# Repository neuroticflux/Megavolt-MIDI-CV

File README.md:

# Megavolt-MIDI-CV
ATmega328-based modular synth MIDI-CV interface

The Megavolt is a MIDI-CV interface featuring two high quality 12-bit CV outputs for note and pitchbend, four 8-bit CV outputs for MIDI CC's, as well as GATE output, two CLOCK outputs and note glide.

12-bit CVs:
CV 1: MIDI note (with glide amount pot)
CV 2: Pitchbend

MIDI NOTE ON triggers the GATE output HIGH. MIDI NOTE OFF triggers it low.

8-bit CVs:
CV 3: CC #01 (Modwheel)
CV 4: CC #04 (Aftertouch/foot controller)
CV 5: CC #16 (General purpose)
CV 6: Velocity

The two CLOCK jacks output 1/1' and 1/16' ticks the from incoming MIDI clock.

A note stack of 4 notes allows several keys to be held down in succession and released to return to the previous note in the stack, allowing for fast playing of arpeggios etc.

The interface is made to hook up to a PSU delivering +/-15V as well as +5V (Synthesizers.com standard).
Current draw untested.

TODO:

- Eurorack compatibility
- Detect MIDI channel on first incoming message
- Reverse voltage protection diodes on input

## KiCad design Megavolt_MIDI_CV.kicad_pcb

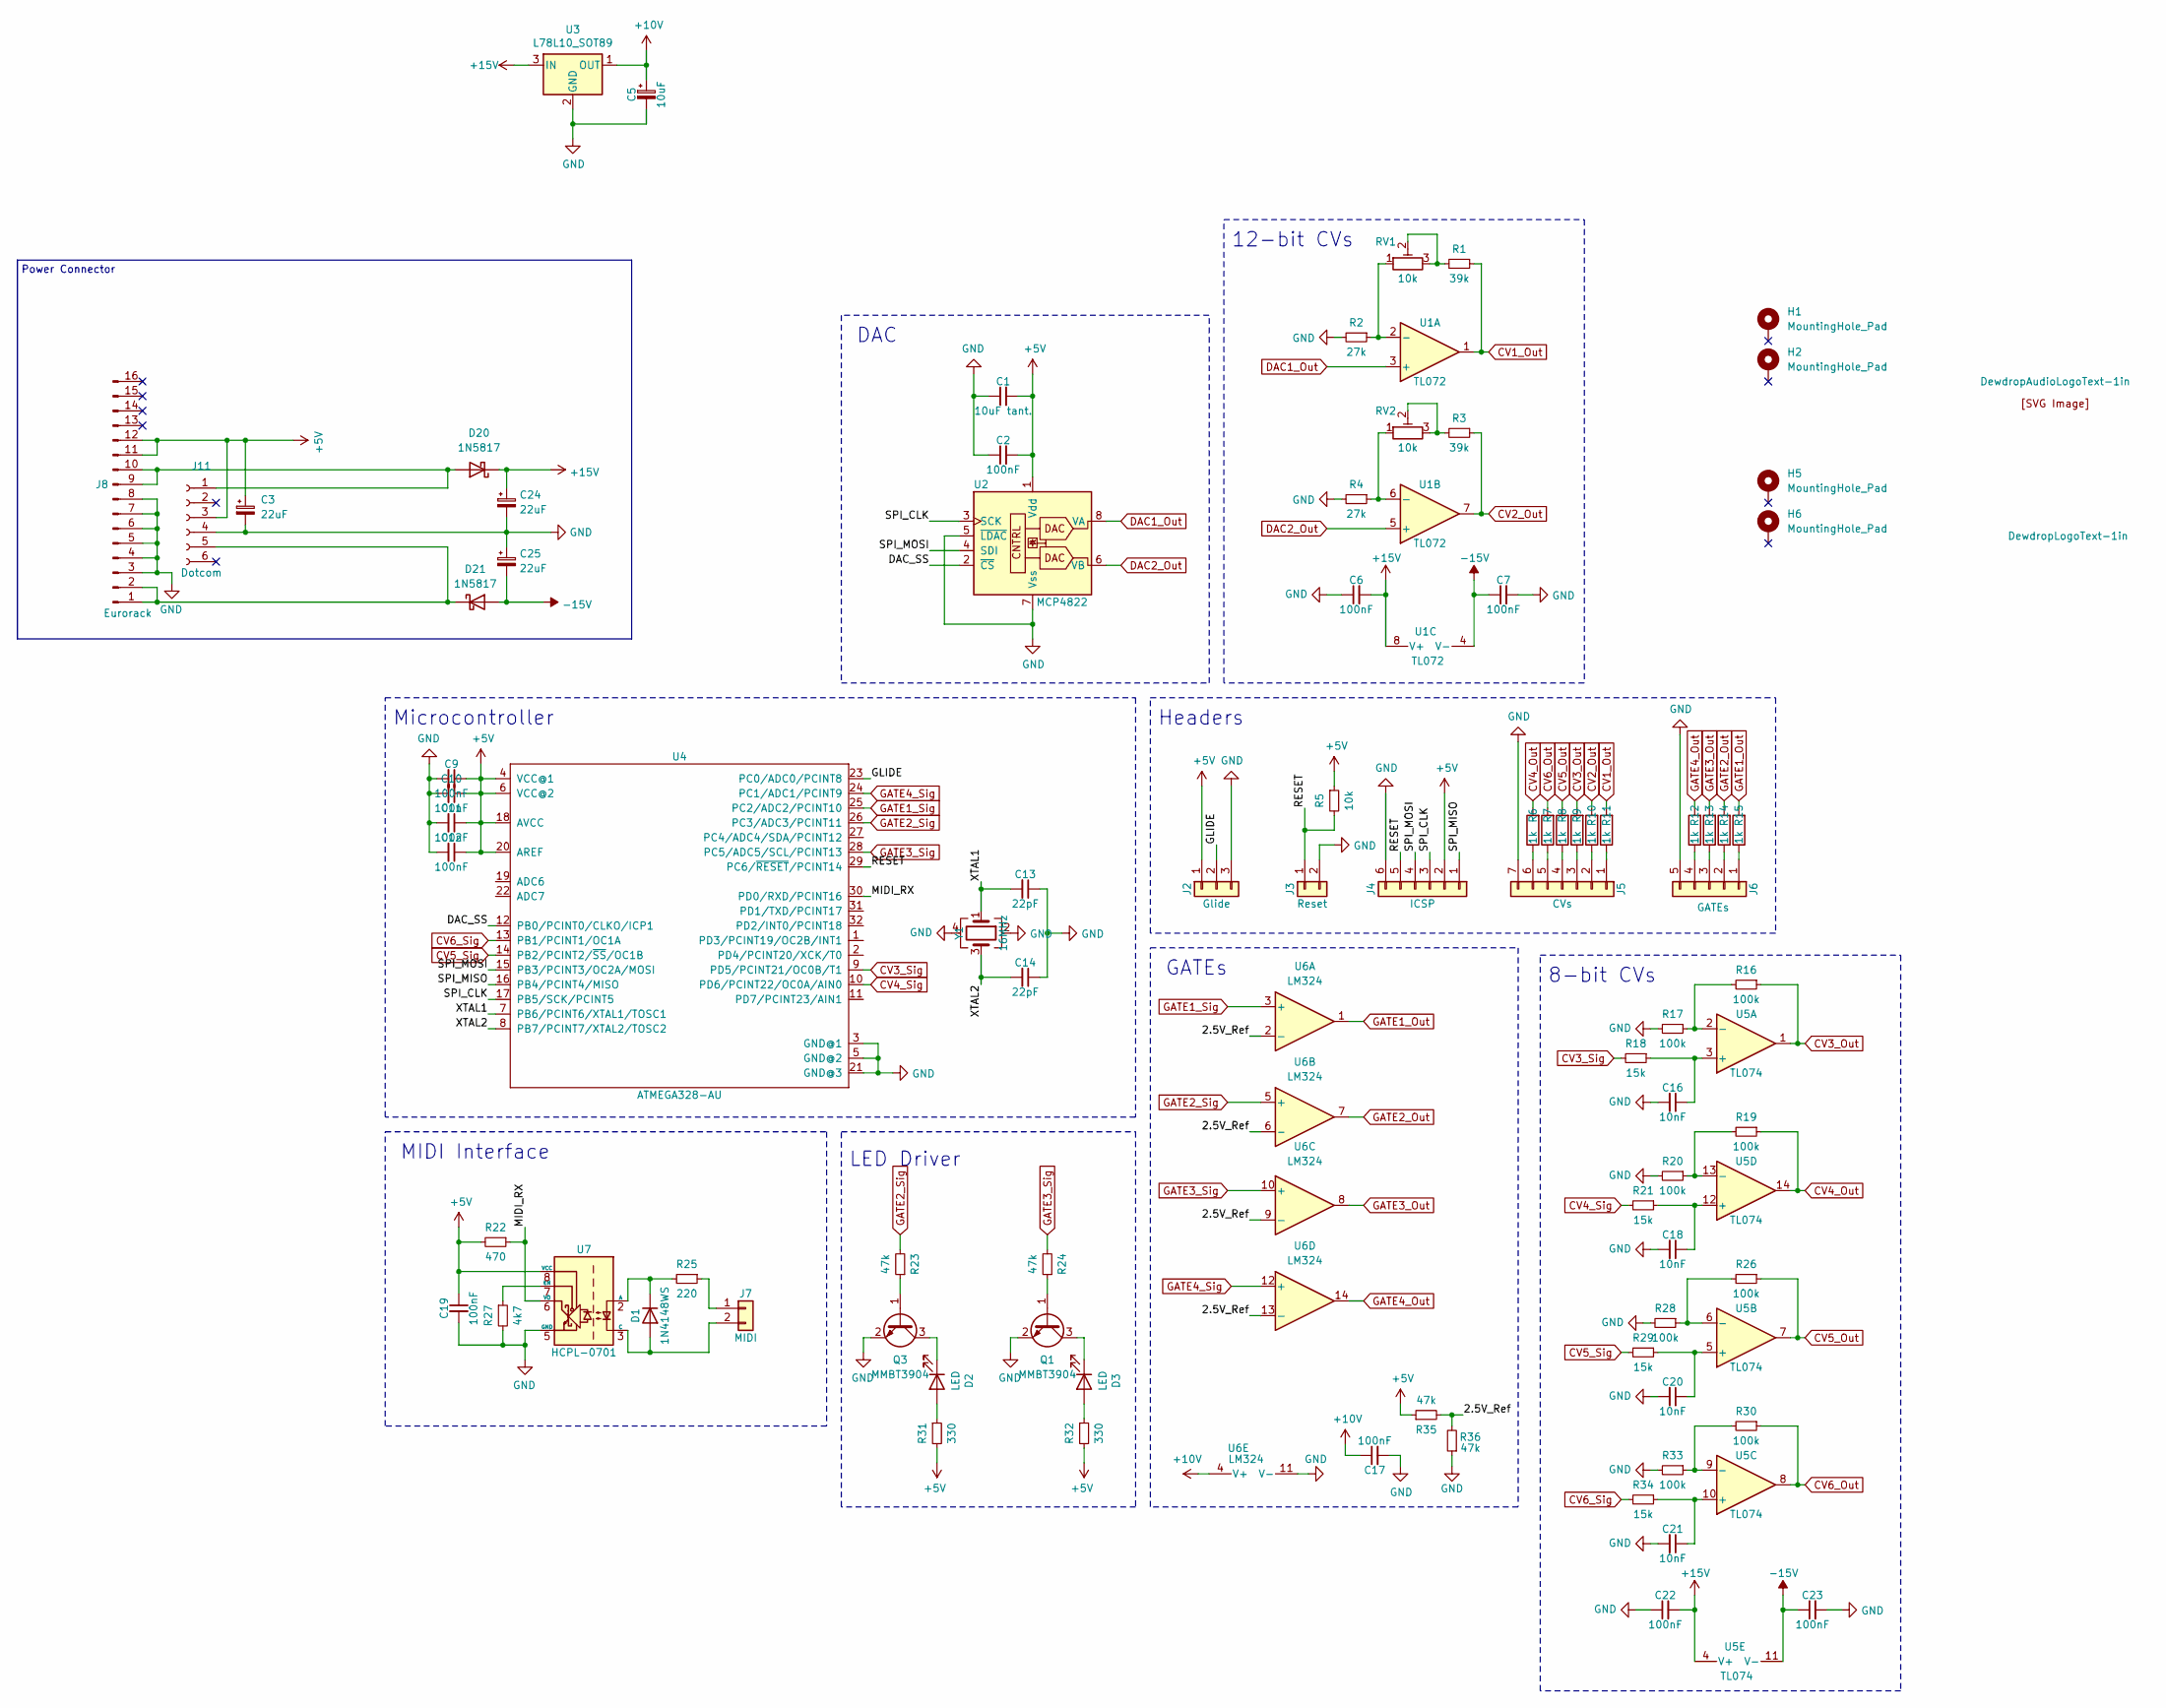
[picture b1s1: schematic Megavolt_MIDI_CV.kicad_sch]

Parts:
C1: 10uF tant.; CP_EIA-3216-18_Kemet-A
C2, C6, C7, C9, C10, C11, C12, C17, C19, C22, C23: 100nF; C_0603_1608Metric
C3, C24, C25: 22uF; CP_Radial_D6.3mm_P2.50mm
C5: 10uF; CP_Radial_D5.0mm_P2.50mm
C13, C14: 22pF; C_0402_1005Metric
C16, C18, C20, C21: 10nF; C_0603_1608Metric
D1: 1N4148WS; D_SOD-323
D2, D3: LED; PinHeader_1x02_P2.54mm_Vertical
D20, D21: 1N5817; D_SOD-123
H1, H2, H5, H6: MountingHole_Pad; MountingHole_3.2mm_M3_DIN965_Pad
J2: Glide; PinHeader_1x03_P2.54mm_Vertical
J3: Reset; PinHeader_1x02_P2.54mm_Vertical
J4: ICSP; PinHeader_2x03_P2.54mm_Vertical
J5: CVs; PinHeader_1x07_P2.54mm_Vertical
J6: GATEs; PinHeader_1x05_P2.54mm_Vertical
J7: MIDI; PinHeader_1x02_P2.54mm_Vertical
J8: Eurorack; PinHeader_2x08_P2.54mm_Vertical
J11: Dotcom; Molex_KK-254_AE-6410-06A_1x06_P2.54mm_Vertical
LOGO2: DewdropLogoText-1in
LOGO3: DewdropAudioLogoText-1in; DewdropAudioLogo-1in
Q1, Q3: MMBT3904; SOT-23
R1, R3: 39k; R_0402_1005Metric
R2, R4: 27k; R_0402_1005Metric
R5: 10k; R_0402_1005Metric
R6, R7, R8, R9, R10, R11, R12, R13, R14, R15: 1k; R_0603_1608Metric
R16, R17, R19, R20, R26, R28, R30, R33: 100k; R_0402_1005Metric
R18, R21, R29, R34: 15k; R_0402_1005Metric
R22: 470; R_0603_1608Metric
R23, R24: 47k; R_0603_1608Metric
R25: 220; R_0402_1005Metric
R27: 4k7; R_0402_1005Metric
R31, R32: 330; R_0805_2012Metric
R35, R36: 47k; R_0402_1005Metric
RV1, RV2: 10k; Potentiometer_Bourns_3314J_Vertical
U1: TL072; SOIC-8_3.9x4.9mm_P1.27mm
U2: MCP4822; SOIC-8_3.9x4.9mm_P1.27mm
U3: L78L10_SOT89; SOT-89-3
U4: ATMEGA328-AU; LQFP-32_7x7mm_P0.8mm
U5: TL074; SOIC-14_3.9x8.7mm_P1.27mm
U6: LM324; SOIC-14_3.9x8.7mm_P1.27mm
U7: HCPL-0701; SOIC-8_3.9x4.9mm_P1.27mm
Y1: 16MHz; Crystal_SMD_3225-4Pin_3.2x2.5mm

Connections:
+5V: C1.2, C2.2, C3.1, C9.1, C10.1, C11.1, C12.1, C19.1, J2.1, J4.2, J8.11, J8.12, J11.3, R5.1, R22.2, R31.2, R32.2, R35.1, U2.1 (Vdd), U4.4 (VCC@1), U4.6 (VCC@2), U4.18 (AVCC), U4.20 (AREF), U7.8 (VCC)
+10V: C5.1, C17.1, U3.1 (OUT), U6.4 (V+)
+15V: C6.2, C22.2, C24.1, D20.1 (K), U1.8 (V+), U3.3 (IN), U5.4 (V+)
-15V: C7.1, C23.1, C25.2, D21.2 (A), U1.4 (V-), U5.11 (V-)
/2.5V_Ref: R35.2, R36.2, U6.2 (-), U6.6 (-), U6.9 (-), U6.13 (-)
/DAC_SS: U2.2 (~CS), U4.12 (PB0/PCINT0/CLKO/ICP1)
/GLIDE: J2.2, U4.23 (PC0/ADC0/PCINT8)
/MIDI_RX: R22.1, U4.30 (PD0/RXD/PCINT16), U7.6 (VO)
/RESET: J3.1, J4.5, R5.2, U4.29 (PC6/~RESET/PCINT14)
/SPI_CLK: J4.3, U2.3 (SCK), U4.17 (PB5/SCK/PCINT5)
/SPI_MISO: J4.1, U4.16 (PB4/PCINT4/MISO)
/SPI_MOSI: J4.4, U2.4 (SDI), U4.15 (PB3/PCINT3/OC2A/MOSI)
/XTAL1: C13.2, U4.7 (PB6/PCINT6/XTAL1/TOSC1), Y1.1
/XTAL2: C14.2, U4.8 (PB7/PCINT7/XTAL2/TOSC2), Y1.3
CV1_Out: R1.1, R11.2, U1.1
CV2_Out: R3.1, R10.2, U1.7
CV3_Out: R9.2, R16.1, U5.1
CV3_Sig: R18.2, U4.9 (PD5/PCINT21/OC0B/T1)
CV4_Out: R6.2, R19.1, U5.14
CV4_Sig: R21.2, U4.10 (PD6/PCINT22/OC0A/AIN0)
CV5_Out: R8.2, R26.1, U5.7
CV5_Sig: R29.2, U4.14 (PB2/PCINT2/~SS/OC1B)
CV6_Out: R7.2, R30.1, U5.8
CV6_Sig: R34.2, U4.13 (PB1/PCINT1/OC1A)
DAC1_Out: U1.3 (+), U2.8 (VA)
DAC2_Out: U1.5 (+), U2.6 (VB)
GATE1_Out: R15.2, U6.1
GATE1_Sig: U4.25 (PC2/ADC2/PCINT10), U6.3 (+)
GATE2_Out: R14.2, U6.7
GATE2_Sig: R23.2, U4.26 (PC3/ADC3/PCINT11), U6.5 (+)
GATE3_Out: R13.2, U6.8
GATE3_Sig: R24.2, U4.28 (PC5/ADC5/SCL/PCINT13), U6.10 (+)
GATE4_Out: R12.2, U6.14
GATE4_Sig: U4.24 (PC1/ADC1/PCINT9), U6.12 (+)
GND: C1.1, C2.1, C3.2, C5.2, C6.1, C7.2, C9.2, C10.2, C11.2, C12.2, C13.1, C14.1, C16.2, C17.2, C18.2, C19.2, C20.2, C21.2, C22.1, C23.2, C24.2, C25.1, J2.3, J3.2, J4.6, J5.7, J6.5, J8.3, J8.4, J8.5, J8.6, J8.7, J8.8, J11.4, Q1.2 (E), Q3.2 (E), R2.2, R4.2, R17.2, R20.2, R27.2, R28.2, R33.2, R36.1, U2.5 (~LDAC), U2.7 (Vss), U3.2 (GND), U4.3 (GND@1), U4.5 (GND@2), U4.21 (GND@3), U6.11 (V-), U7.5 (GND), Y1.2, Y1.4
unnamed: D1.2 (A), J7.2, U7.3 (C)
unnamed: D1.1 (K), R25.2, U7.2 (A)
unnamed: D2.2 (A), R31.1
unnamed: D2.1 (K), Q3.3 (C)
unnamed: D3.2 (A), R32.1
unnamed: D3.1 (K), Q1.3 (C)
unnamed: D20.2 (A), J8.9, J8.10, J11.1
unnamed: D21.1 (K), J8.1, J8.2, J11.5
unnamed: J5.1, R11.1
unnamed: J5.2, R10.1
unnamed: J5.3, R9.1
unnamed: J5.4, R8.1
unnamed: J5.5, R7.1
unnamed: J5.6, R6.1
unnamed: J6.1, R15.1
unnamed: J6.2, R14.1
unnamed: J6.3, R13.1
unnamed: J6.4, R12.1
unnamed: J7.1, R25.1
unnamed: Q1.1 (B), R24.1
unnamed: Q3.1 (B), R23.1
unnamed: R1.2, RV1.2, RV1.3
unnamed: R3.2, RV2.2, RV2.3
unnamed: R2.1, RV1.1, U1.2 (-)
unnamed: R4.1, RV2.1, U1.6 (-)
unnamed: C16.1, R18.1, U5.3 (+)
unnamed: R16.2, R17.1, U5.2 (-)
unnamed: C20.1, R29.1, U5.5 (+)
unnamed: R26.2, R28.1, U5.6 (-)
unnamed: C21.1, R34.1, U5.10 (+)
unnamed: R30.2, R33.1, U5.9 (-)
unnamed: C18.1, R21.1, U5.12 (+)
unnamed: R19.2, R20.1, U5.13 (-)
unnamed: R27.1, U7.7 (EN)

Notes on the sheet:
Headers
8-bit CVs
Microcontroller
GATEs
Power Connector
DAC
LED Driver
12-bit CVs
MIDI Interface

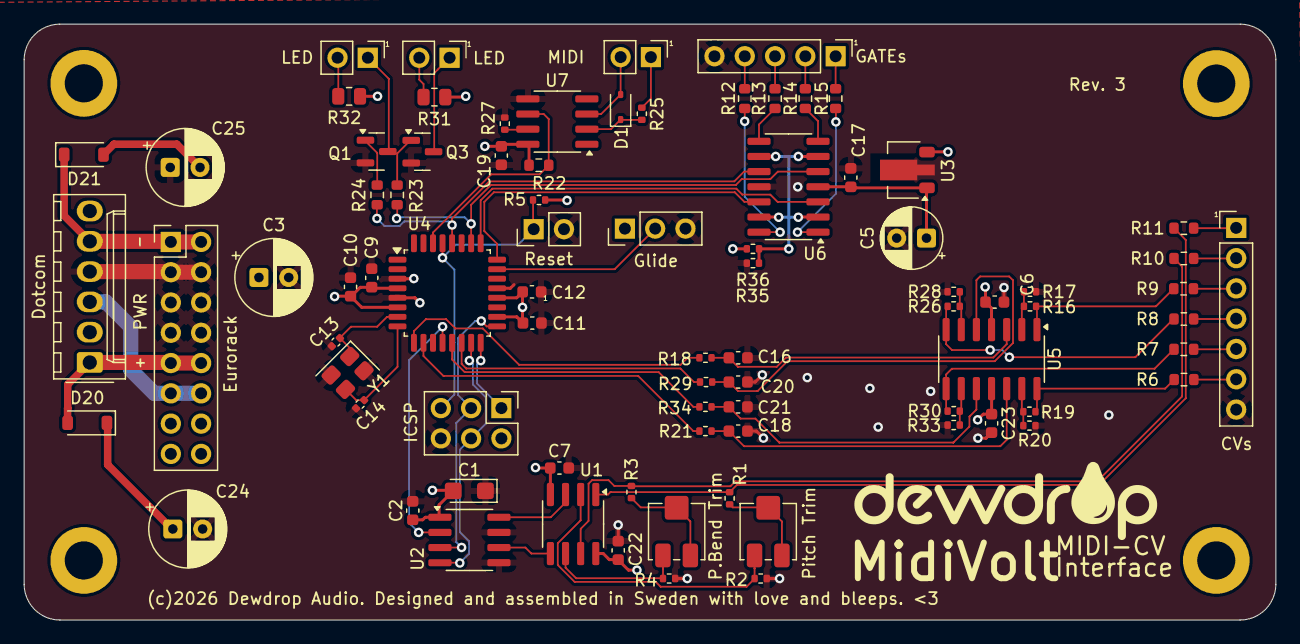
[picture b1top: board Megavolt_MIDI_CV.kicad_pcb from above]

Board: 4 copper layers, 105.0 x 50.0 mm, 89 parts (1 on the bottom side), 69 nets.

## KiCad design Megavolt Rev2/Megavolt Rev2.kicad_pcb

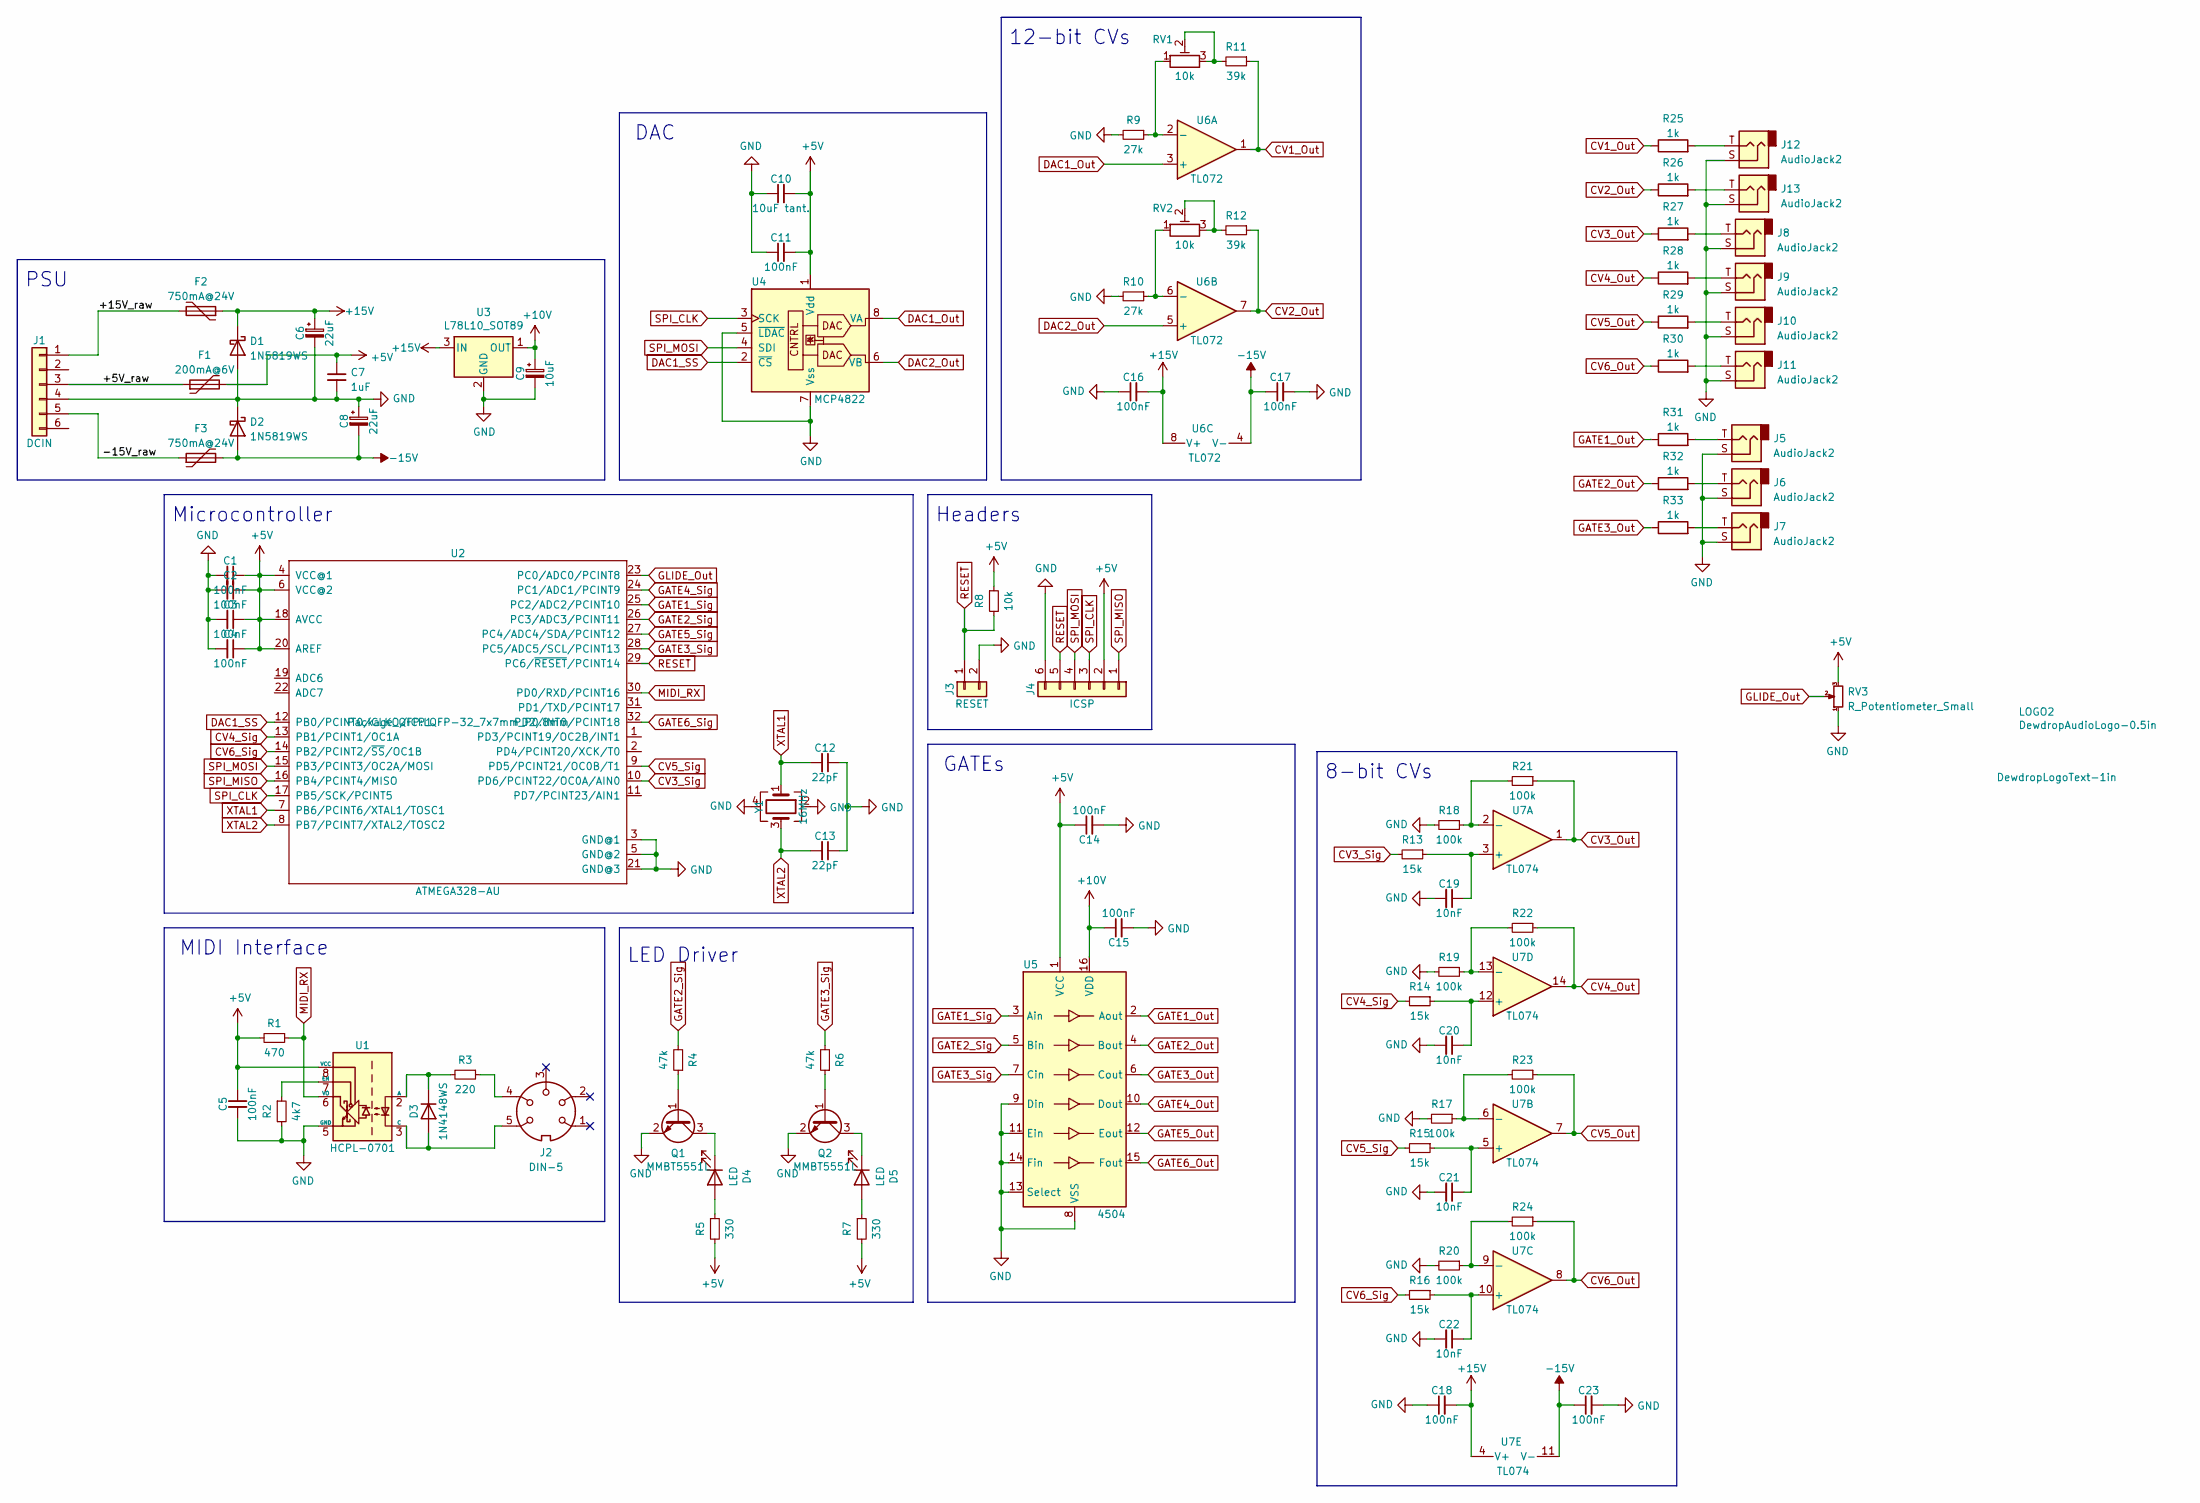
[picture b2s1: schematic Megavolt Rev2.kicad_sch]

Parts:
C1, C2, C3, C4, C5, C11, C14, C15, C16, C17, C18, C23: 100nF; C_0603_1608Metric
C6, C8: 22uF; CP_Radial_D5.0mm_P2.50mm
C7: 1uF; C_0805_2012Metric
C9: 10uF; CP_Radial_D5.0mm_P2.50mm
C10: 10uF tant.; CP_EIA-3216-18_Kemet-A
C12, C13: 22pF; C_0402_1005Metric
C19, C20, C21, C22: 10nF; C_0603_1608Metric
D1, D2: 1N5819WS; D_SOD-323
D3: 1N4148WS; D_SOD-323
D4, D5: LED; LED_D5.0mm
F1: 200mA@6V; Fuse_0402_1005Metric
F2, F3: 750mA@24V; Fuse_1812_4532Metric
J1: DCIN; Molex_KK-254_AE-6410-06A_1x06_P2.54mm_Vertical
J2: DIN-5; Switchcraft 57NC5FX
J3: RESET; PinHeader_1x02_P2.54mm_Vertical
J4: ICSP; PinHeader_2x03_P2.54mm_Vertical
J5, J6, J7, J8, J9, J10, J11, J12, J13: AudioJack2; Amphenol AJCM-MN-2
LOGO1: DewdropLogoText-1in
LOGO2: DewdropAudioLogo-0.5in
Q1, Q2: MMBT5551L; SOT-23
R1: 470; R_0603_1608Metric
R2: 4k7; R_0603_1608Metric
R3: 220; R_0603_1608Metric
R4, R6: 47k; R_0603_1608Metric
R5, R7: 330; R_0603_1608Metric
R8: 10k; R_0603_1608Metric
R9, R10: 27k; R_0603_1608Metric
R11, R12: 39k; R_0603_1608Metric
R13, R14, R15, R16: 15k; R_0603_1608Metric
R17, R18, R19, R20, R21, R22, R23, R24: 100k; R_0603_1608Metric
R25, R26, R27, R28, R29, R30, R31, R32, R33: 1k; R_0603_1608Metric
RV1, RV2: 10k; Potentiometer_Bourns_3314G_Vertical
RV3: R_Potentiometer_Small; Potentiometer_Alps_RK09L_Single_Vertical
U1: HCPL-0701; SOIC-8_3.9x4.9mm_P1.27mm
U2: ATMEGA328-AU; LQFP-32_7x7mm_P0.8mm
U3: L78L10_SOT89; SOT-89-3
U4: MCP4822; SOIC-8_3.9x4.9mm_P1.27mm
U5: 4504; SOIC-16_3.9x9.9mm_P1.27mm
U6: TL072; SOIC-8_3.9x4.9mm_P1.27mm
U7: TL074; SOIC-14_3.9x8.7mm_P1.27mm
Y1: 16MHz; Crystal_SMD_3225-4Pin_3.2x2.5mm

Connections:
+5V: C1.1, C2.1, C3.1, C4.1, C5.1, C7.1, C10.2, C11.2, C14.1, F1.2, J4.2, R1.2, R5.2, R7.2, R8.1, RV3.3, U1.8 (VCC), U2.4 (VCC@1), U2.6 (VCC@2), U2.18 (AVCC), U2.20 (AREF), U4.1 (Vdd), U5.1 (VCC)
+10V: C9.1, C15.1, U3.1 (OUT), U5.16 (VDD)
+15V: C6.1, C16.2, C18.2, D1.1 (K), F2.1, U3.3 (IN), U6.8 (V+), U7.4 (V+)
-15V: C8.2, C17.1, C23.1, D2.2 (A), F3.2, U6.4 (V-), U7.11 (V-)
/+5V_raw: F1.1, J1.3
/+15V_raw: F2.2, J1.1
/-15V_raw: F3.1, J1.5
CV1_Out: R11.1, R25.1, U6.1
CV2_Out: R12.1, R26.1, U6.7
CV3_Out: R21.1, R27.1, U7.1
CV3_Sig: R13.2, U2.10 (PD6/PCINT22/OC0A/AIN0)
CV4_Out: R22.1, R28.1, U7.14
CV4_Sig: R14.2, U2.13 (PB1/PCINT1/OC1A)
CV5_Out: R23.1, R29.1, U7.7
CV5_Sig: R15.2, U2.9 (PD5/PCINT21/OC0B/T1)
CV6_Out: R24.1, R30.1, U7.8
CV6_Sig: R16.2, U2.14 (PB2/PCINT2/~SS/OC1B)
DAC1_Out: U4.8 (VA), U6.3 (+)
DAC1_SS: U2.12 (PB0/PCINT0/CLKO/ICP1), U4.2 (~CS)
DAC2_Out: U4.6 (VB), U6.5 (+)
GATE1_Out: R31.1, U5.2 (Aout)
GATE1_Sig: U2.25 (PC2/ADC2/PCINT10), U5.3 (Ain)
GATE2_Out: R32.1, U5.4 (Bout)
GATE2_Sig: R4.2, U2.26 (PC3/ADC3/PCINT11), U5.5 (Bin)
GATE3_Out: R33.1, U5.6 (Cout)
GATE3_Sig: R6.2, U2.28 (PC5/ADC5/SCL/PCINT13), U5.7 (Cin)
GATE4_Out: U5.10 (Dout)
GATE4_Sig: U2.24 (PC1/ADC1/PCINT9)
GATE5_Out: U5.12 (Eout)
GATE5_Sig: U2.27 (PC4/ADC4/SDA/PCINT12)
GATE6_Out: U5.15 (Fout)
GATE6_Sig: U2.32 (PD2/INT0/PCINT18)
GLIDE_Out: RV3.2, U2.23 (PC0/ADC0/PCINT8)
GND: C1.2, C2.2, C3.2, C4.2, C5.2, C6.2, C7.2, C8.1, C9.2, C10.1, C11.1, C12.1, C13.1, C14.2, C15.2, C16.1, C17.2, C18.1, C19.2, C20.2, C21.2, C22.2, C23.2, D1.2 (A), D2.1 (K), J1.4, J3.2, J4.6, J5.S, J6.S, J7.S, J8.S, J9.S, J10.S, J11.S, J12.S, J13.S, Q1.2 (E), Q2.2 (E), R2.2, R9.2, R10.2, R17.2, R18.2, R19.2, R20.2, RV3.1, U1.5 (GND), U2.3 (GND@1), U2.5 (GND@2), U2.21 (GND@3), U3.2 (GND), U4.5 (~LDAC), U4.7 (Vss), U5.8 (VSS), U5.9 (Din), U5.11 (Ein), U5.13 (Select), U5.14 (Fin), Y1.2, Y1.4
MIDI_RX: R1.1, U1.6 (VO), U2.30 (PD0/RXD/PCINT16)
unnamed: C19.1, R13.1, U7.3 (+)
unnamed: C20.1, R14.1, U7.12 (+)
unnamed: C21.1, R15.1, U7.5 (+)
unnamed: C22.1, R16.1, U7.10 (+)
unnamed: D3.1 (K), R3.2, U1.2 (A)
unnamed: D3.2 (A), J2.5, U1.3 (C)
unnamed: D4.1 (K), Q1.3 (C)
unnamed: D4.2 (A), R5.1
unnamed: D5.1 (K), Q2.3 (C)
unnamed: D5.2 (A), R7.1
unnamed: J2.4, R3.1
unnamed: J5.T, R31.2
unnamed: J6.T, R32.2
unnamed: J7.T, R33.2
unnamed: J8.T, R27.2
unnamed: J9.T, R28.2
unnamed: J10.T, R29.2
unnamed: J11.T, R30.2
unnamed: J12.T, R25.2
unnamed: J13.T, R26.2
unnamed: Q1.1 (B), R4.1
unnamed: Q2.1 (B), R6.1
unnamed: R2.1, U1.7 (EN)
unnamed: R9.1, RV1.1, U6.2 (-)
unnamed: R10.1, RV2.1, U6.6 (-)
unnamed: R11.2, RV1.2, RV1.3
unnamed: R12.2, RV2.2, RV2.3
unnamed: R17.1, R23.2, U7.6 (-)
unnamed: R18.1, R21.2, U7.2 (-)
unnamed: R19.1, R22.2, U7.13 (-)
unnamed: R20.1, R24.2, U7.9 (-)
RESET: J3.1, J4.5, R8.2, U2.29 (PC6/~RESET/PCINT14)
SPI_CLK: J4.3, U2.17 (PB5/SCK/PCINT5), U4.3 (SCK)
SPI_MISO: J4.1, U2.16 (PB4/PCINT4/MISO)
SPI_MOSI: J4.4, U2.15 (PB3/PCINT3/OC2A/MOSI), U4.4 (SDI)
XTAL1: C12.2, U2.7 (PB6/PCINT6/XTAL1/TOSC1), Y1.1
XTAL2: C13.2, U2.8 (PB7/PCINT7/XTAL2/TOSC2), Y1.3

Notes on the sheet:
Headers
8-bit CVs
Microcontroller
GATEs
DAC
LED Driver
12-bit CVs
MIDI Interface
PSU

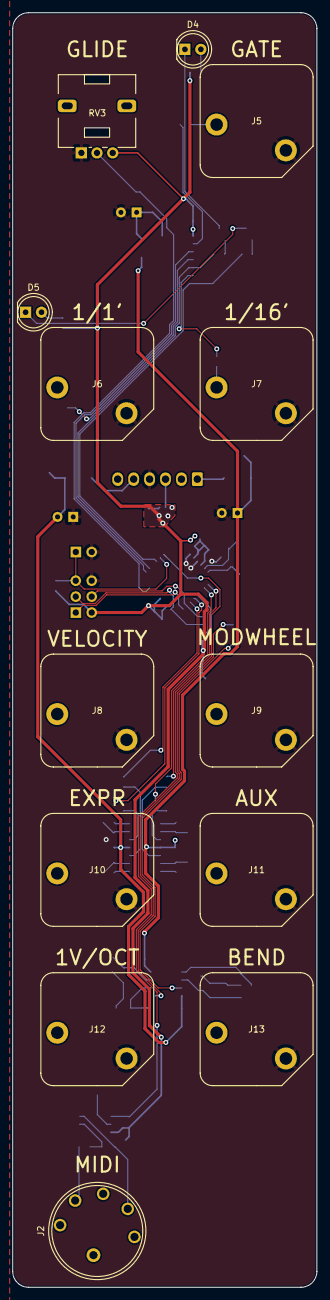
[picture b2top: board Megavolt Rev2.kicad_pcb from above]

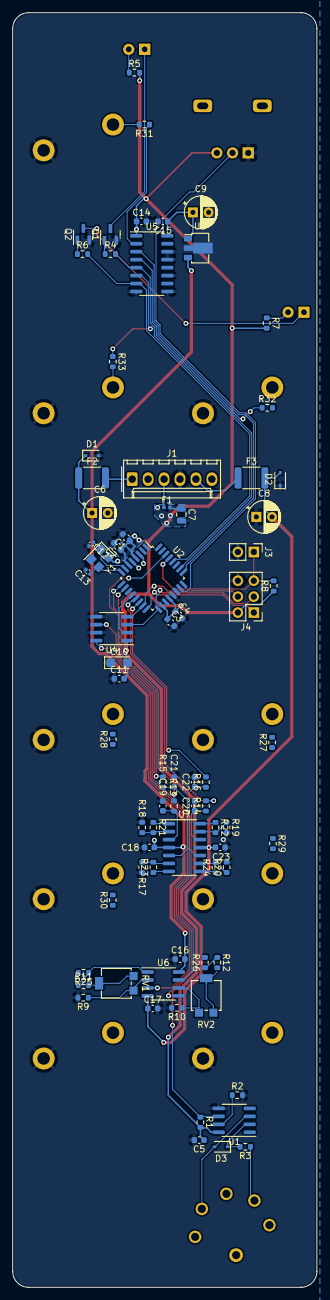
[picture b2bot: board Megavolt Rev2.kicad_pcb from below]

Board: 2 copper layers, 48.5 x 203.2 mm, 92 parts (78 on the bottom side), 66 nets.

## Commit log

2018-03-22 Added files
2018-03-22 Added images for home etching
2018-03-25 v2 board update
2018-03-25 Firmware
2020-11-26 Rev.1a-compatible firmware
2020-11-26 Rev.1a board + schematic
2022-11-19 Rev.2 files, update to KiCad6
2022-12-17 Firmware bugfixes, Rev.2 board compatibility
2022-12-19 Auto-detect MIDI channel, pitch bend on CV2 out, bugfixes
2022-12-25 Rev.3 WIP
2026-04-03 Removed old project, updated to Rev. 2b
2026-04-03 Firmware update, working 1/16' clock out
2026-04-03 Fixed typo on front panel
2026-05-07 Eurorack panel
2026-05-10 Panel updates
2026-05-10 Rev. 3 WIP
2026-05-12 1/16, 1/4 and 1/1 clocks working. Changed some port ID's for Rev. 3
2026-05-12 Implemented the better glide from Quaint (temporarily 32-bit)
2026-05-12 Switched to Q15 internally, added bend to pitch out
2026-05-12 Changed aux CV out pins for Rev. 3

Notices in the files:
Megavolt Rev2/Megavolt Rev2.kicad_pcb:
(c)2021 Dewdrop Audio. All rights reserved. Designed and assembled in Sweden with love and bleeps. <3
Megavolt_MIDI_CV.kicad_pcb:
(c)2026 Dewdrop Audio. Designed and assembled in Sweden with love and bleeps. <3
